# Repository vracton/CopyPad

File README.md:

# CopyPad

A custom macropad designed for efficient copy, cut, and paste with an integrated OLED display and rotary encoder for volume control.

## Features

- **3-Key Linear Layout**: Keys for Cut (Ctrl+X), Copy (Ctrl+C), and Paste (Ctrl+V)
- **OLED Display**: 128x32 pixel display showing current status
- **Rotary Encoder**: Volume control with tactile feedback
- **Open Source**: Complete hardware and software design files included

*physical picture available soon*

## Project Structure

```
CopyPad/
├── README.md               
├── cad/                    
│   └── CopyPad_v2.step     
├── firmware/                
│   └── main.py             
├── pcb/                    
│   ├── CopyPad.kicad_pcb   
│   ├── CopyPad.kicad_sch   
│   ├── CopyPad.kicad_pro   
│   ├── CopyPad.kicad_prl   
│   └── library/            
└── production/             
    ├── CopyPad_main.stl    
    ├── CopyPad_top.stl     
    └── gerbers.zip         
```

## Assembly

1. Solder all components according to the schematic
2. Flash `main.py` to the microcontroller
3. 3D print the case files from `production/CopyPad_main.stl` and `production/CopyPad_top.stl`
4. Install the PCB into the case
5. Secure the top case with heatset inserts and screws

## Bill of Materials

| Component | Quantity | Description |
|-----------|----------|-------------|
| PCB | 1 | Manufactured from provided Gerber files |
| Seeed XIAO RP2040 | 1 |  |
| MX-Style switches | 3 |  |
| Keycaps | 3 | X, C, V legends preferred |
| SK6812 MINI-E LEDs | 3 | RGB! |
| 0.91 inch OLED displays  | 1 | GND-VCC-SCL-SDA pin order |
| Rotary Encoder  | 1 | EC11 |
| Encoder Knob | 1 |  |
| Case | 1 | 3D printed from provided STL files |
| Heatset Inserts | 4 | M3x5mx4mm |
| Screws | 4 | M3x16mm |
| Soldering Iron | 1 | For Assembly |

## Pictures

## License

This project is open source and available under the MIT License. See the LICENSE file for more details.

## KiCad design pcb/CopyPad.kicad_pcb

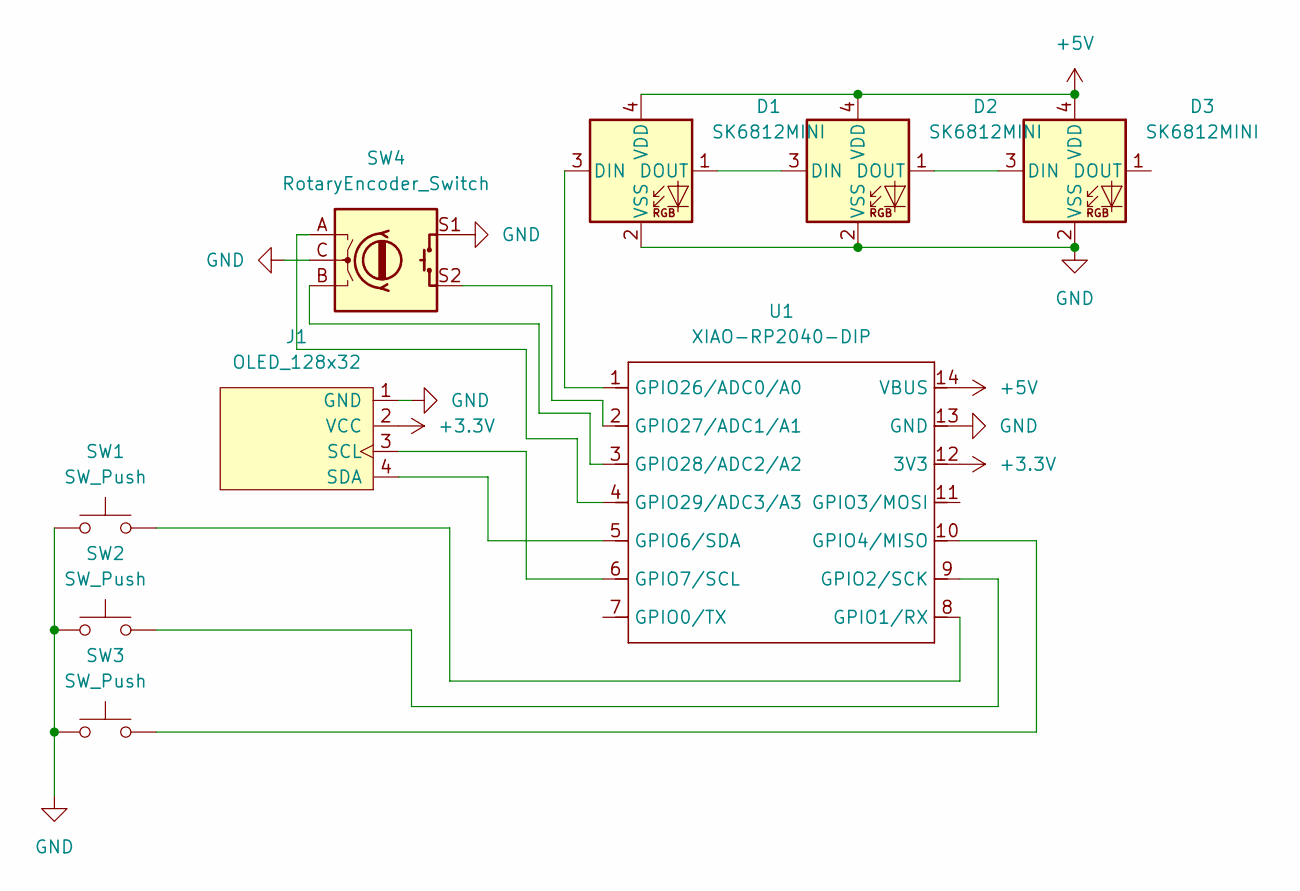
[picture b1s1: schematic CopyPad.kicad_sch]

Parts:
D1, D2, D3: SK6812MINI; LED_SK6812MINI_PLCC4_3.5x3.5mm_P1.75mm
J1: OLED_128x32; SSD1306-0.91-OLED-4pin-128x32
SW1, SW2, SW3: SW_Push; SW_Cherry_MX_1.00u_PCB
SW4: RotaryEncoder_Switch; RotaryEncoder_Alps_EC11E_Vertical_H20mm
U1: XIAO-RP2040-DIP

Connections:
+3.3V: J1.2 (VCC), U1.12 (3V3)
+5V: D1.4 (VDD), D2.4 (VDD), D3.4 (VDD), U1.14 (VBUS)
GND: D1.2 (VSS), D2.2 (VSS), D3.2 (VSS), J1.1 (GND), SW1.1, SW2.1, SW3.1, SW4.C, SW4.S1, U1.13 (GND)
unnamed: D1.3 (DIN), U1.1 (GPIO26/ADC0/A0)
unnamed: D1.1 (DOUT), D2.3 (DIN)
unnamed: D2.1 (DOUT), D3.3 (DIN)
unnamed: J1.3 (SCL), U1.6 (GPIO7/SCL)
unnamed: J1.4 (SDA), U1.5 (GPIO6/SDA)
unnamed: SW1.2, U1.8 (GPIO1/RX)
unnamed: SW2.2, U1.9 (GPIO2/SCK)
unnamed: SW3.2, U1.10 (GPIO4/MISO)
unnamed: SW4.S2, U1.2 (GPIO27/ADC1/A1)
unnamed: SW4.B, U1.3 (GPIO28/ADC2/A2)
unnamed: SW4.A, U1.4 (GPIO29/ADC3/A3)

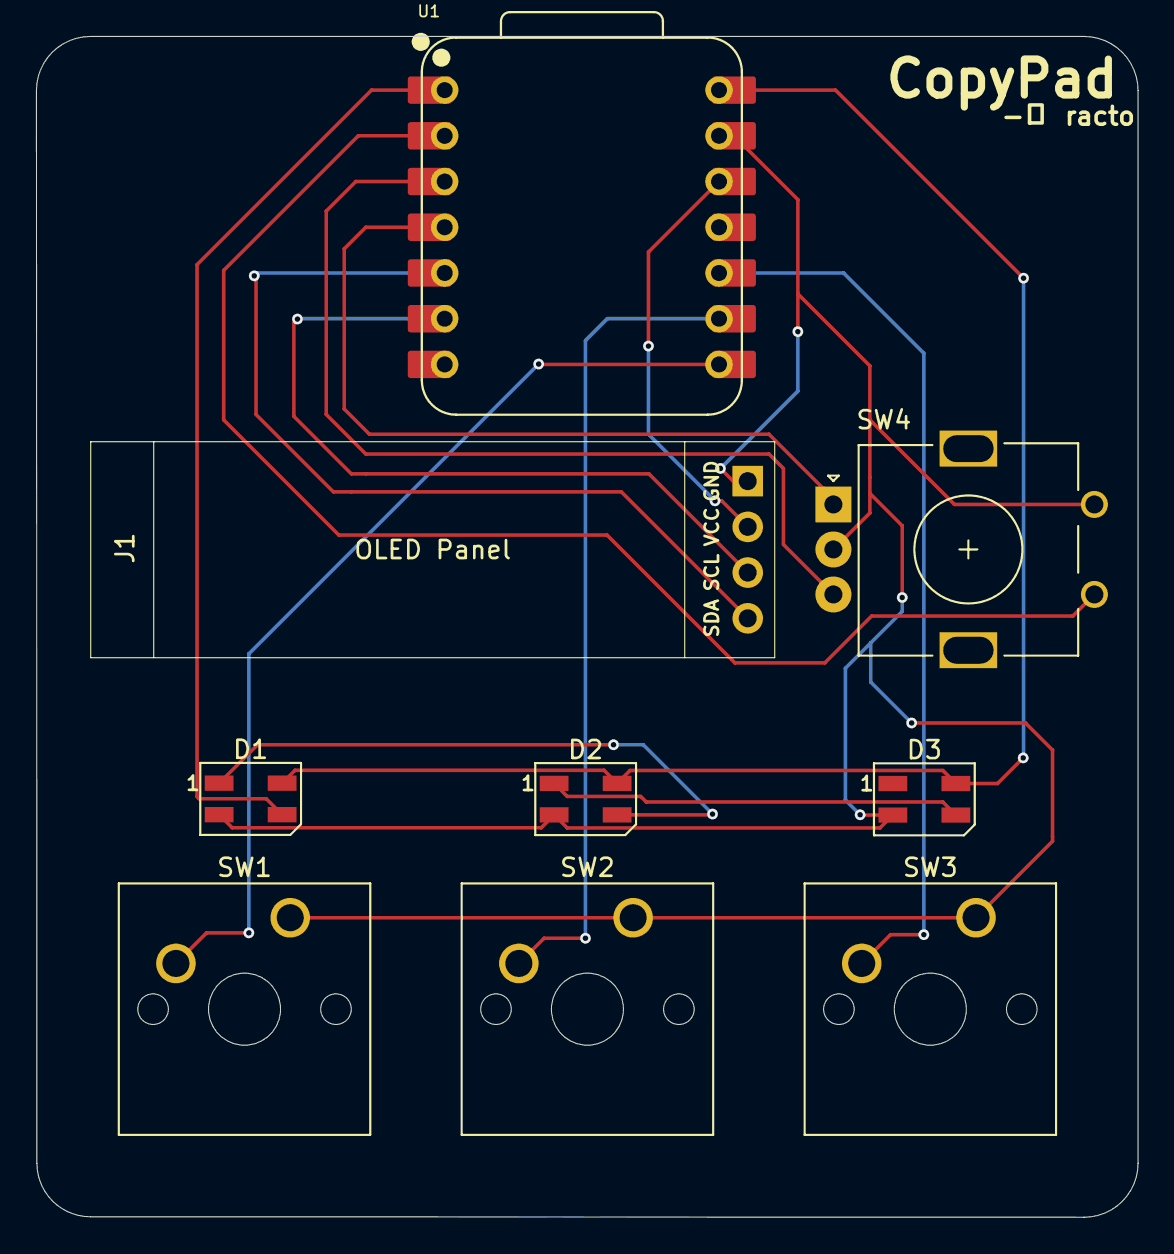
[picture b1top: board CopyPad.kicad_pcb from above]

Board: 2 copper layers, 61.2 x 65.6 mm, 9 parts (0 on the bottom side), 14 nets.

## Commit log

2025-06-13 CopyPad v1
2025-06-18 update to replace SK6812 with SK6812 MINI
2025-06-18 Fix firmware to press ctrl+x/c/v
